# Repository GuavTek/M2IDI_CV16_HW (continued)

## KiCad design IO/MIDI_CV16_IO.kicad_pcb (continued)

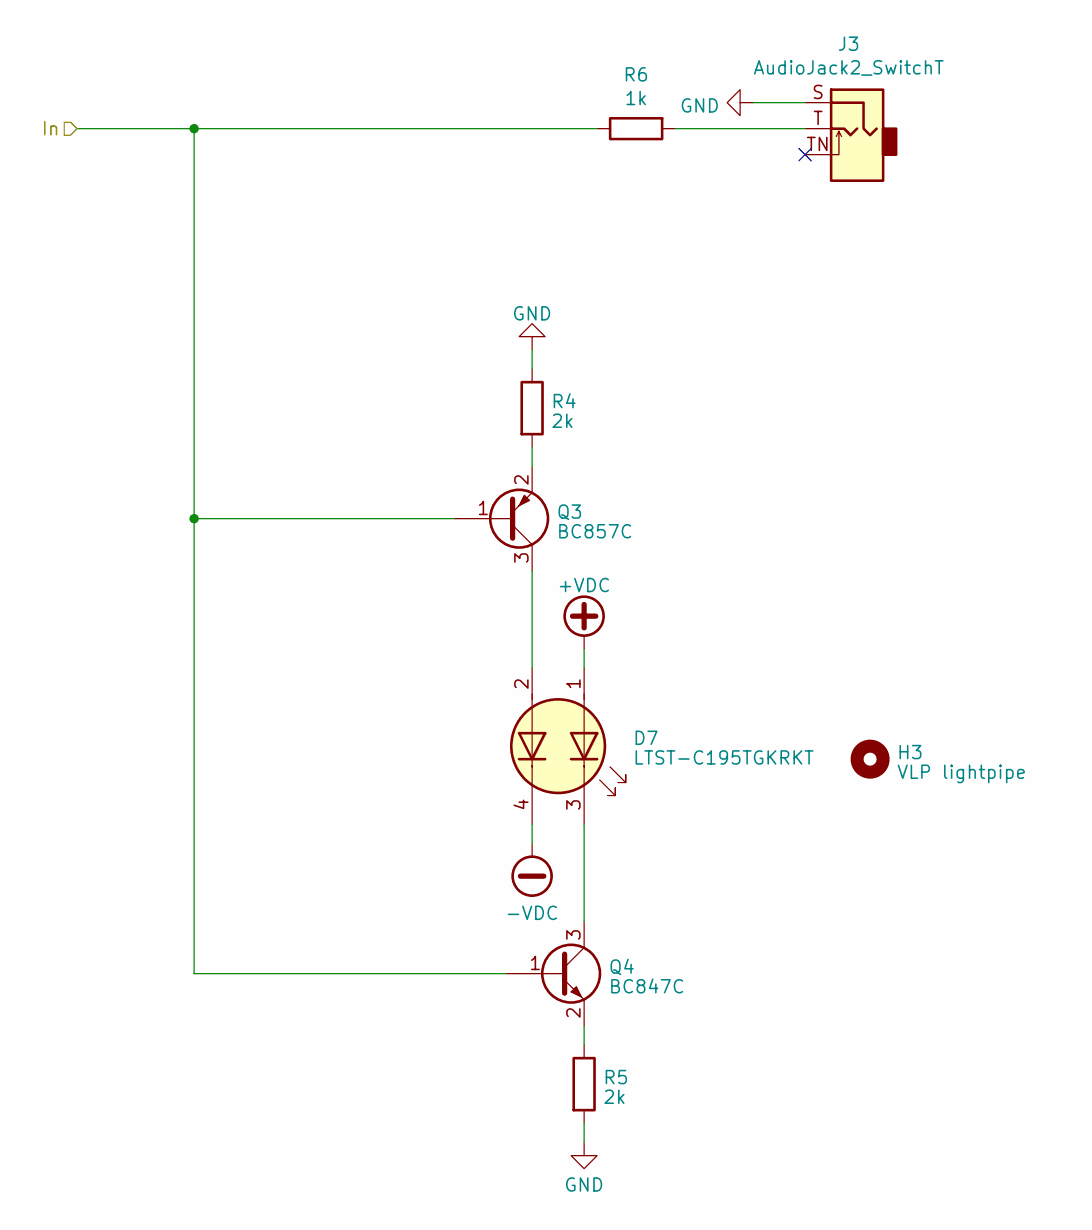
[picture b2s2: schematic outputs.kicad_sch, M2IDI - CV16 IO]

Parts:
D7: LTST-C195TGKRKT; LED_LiteOn_LTST-C195TGKRKT
H3: VLP lightpipe; VLP-LightPipes
J3: AudioJack2_SwitchT; PJ398SM
Q3: BC857C; SOT-23
Q4: BC847C; SOT-23
R4, R5: 2k; R_0603_1608Metric
R6: 1k; R_0603_1608Metric

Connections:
+VDC: D7.1 (A1); also elsewhere on the board
-VDC: D7.4 (K2); also elsewhere on the board
/Outputs1/In: Q3.1 (B), Q4.1 (B), R6.1; also elsewhere on the board
GND: J3.S, R4.1, R5.2; also elsewhere on the board
unnamed: D7.2 (A2), Q3.3 (C)
unnamed: D7.3 (K1), Q4.3 (C)
unnamed: J3.T, R6.2
unnamed: Q3.2 (E), R4.2
unnamed: Q4.2 (E), R5.1

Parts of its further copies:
D10, D13, D16, D19, D61, D64, D67, D70, D73, D76, D79, D82, D85, D88, D91: LTST-C195TGKRKT; LED_LiteOn_LTST-C195TGKRKT
H1, H2, H4, H5, H6, H7, H8, H9, H10, H11, H12, H13, H14, H15, H16: VLP lightpipe; VLP-LightPipes
J4, J5, J6, J7, J8, J9, J10, J12, J13, J14, J15, J16, J17, J18, J19: AudioJack2_SwitchT; PJ398SM
Q5, Q7, Q9, Q11, Q13, Q15, Q17, Q19, Q21, Q23, Q25, Q27, Q29, Q31, Q33: BC857C; SOT-23
Q6, Q8, Q10, Q12, Q14, Q16, Q18, Q20, Q22, Q24, Q26, Q28, Q30, Q32, Q34: BC847C; SOT-23
R7, R8, R10, R11, R13, R14, R16, R17, R19, R20, R22, R23, R25, R26, R28, R29, R31, R32, R34, R35, R37, R38, R40, R41, R43, R44, R46, R47, R49, R50: 2k; R_0603_1608Metric
R9, R12, R15, R18, R21, R24, R27, R30, R33, R36, R39, R42, R45, R48, R51: 1k; R_0603_1608Metric

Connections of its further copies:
+VDC: D10.1 (A1), D13.1 (A1), D16.1 (A1), D19.1 (A1), D61.1 (A1), D64.1 (A1), D67.1 (A1), D70.1 (A1), D73.1 (A1), D76.1 (A1), D79.1 (A1), D82.1 (A1), D85.1 (A1), D88.1 (A1), D91.1 (A1); also elsewhere on the board
-VDC: D10.4 (K2), D13.4 (K2), D16.4 (K2), D19.4 (K2), D61.4 (K2), D64.4 (K2), D67.4 (K2), D70.4 (K2), D73.4 (K2), D76.4 (K2), D79.4 (K2), D82.4 (K2), D85.4 (K2), D88.4 (K2), D91.4 (K2); also elsewhere on the board
/Outputs2/In: Q5.1 (B), Q6.1 (B), R9.1; also elsewhere on the board
/Outputs3/In: Q7.1 (B), Q8.1 (B), R12.1; also elsewhere on the board
/Outputs4/In: Q9.1 (B), Q10.1 (B), R15.1; also elsewhere on the board
/Outputs5/In: Q11.1 (B), Q12.1 (B), R18.1; also elsewhere on the board
/Outputs6/In: Q13.1 (B), Q14.1 (B), R21.1; also elsewhere on the board
/Outputs7/In: Q15.1 (B), Q16.1 (B), R24.1; also elsewhere on the board
/Outputs8/In: Q17.1 (B), Q18.1 (B), R27.1; also elsewhere on the board
/Outputs9/In: Q19.1 (B), Q20.1 (B), R30.1; also elsewhere on the board
/Outputs10/In: Q21.1 (B), Q22.1 (B), R33.1; also elsewhere on the board
/Outputs11/In: Q23.1 (B), Q24.1 (B), R36.1; also elsewhere on the board
/Outputs12/In: Q25.1 (B), Q26.1 (B), R39.1; also elsewhere on the board
/Outputs13/In: Q27.1 (B), Q28.1 (B), R42.1; also elsewhere on the board
/Outputs14/In: Q29.1 (B), Q30.1 (B), R45.1; also elsewhere on the board
/Outputs15/In: Q31.1 (B), Q32.1 (B), R48.1; also elsewhere on the board
/Outputs16/In: Q33.1 (B), Q34.1 (B), R51.1; also elsewhere on the board
GND: J4.S, J5.S, J6.S, J7.S, J8.S, J9.S, J10.S, J12.S, J13.S, J14.S, J15.S, J16.S, J17.S, J18.S, J19.S, R7.1, R8.2, R10.1, R11.2, R13.1, R14.2, R16.1, R17.2, R19.1, R20.2, R22.1, R23.2, R25.1, R26.2, R28.1, R29.2, R31.1, R32.2, R34.1, R35.2, R37.1, R38.2, R40.1, R41.2, R43.1, R44.2, R46.1, R47.2, R49.1, R50.2; also elsewhere on the board
unnamed: D10.2 (A2), Q5.3 (C)
unnamed: D10.3 (K1), Q6.3 (C)
unnamed: D13.2 (A2), Q7.3 (C)
unnamed: D13.3 (K1), Q8.3 (C)
unnamed: D16.2 (A2), Q9.3 (C)
unnamed: D16.3 (K1), Q10.3 (C)
unnamed: D19.2 (A2), Q11.3 (C)
unnamed: D19.3 (K1), Q12.3 (C)
unnamed: D61.2 (A2), Q13.3 (C)
unnamed: D61.3 (K1), Q14.3 (C)
unnamed: D64.2 (A2), Q15.3 (C)
unnamed: D64.3 (K1), Q16.3 (C)
unnamed: D67.2 (A2), Q17.3 (C)
unnamed: D67.3 (K1), Q18.3 (C)
unnamed: D70.2 (A2), Q19.3 (C)
unnamed: D70.3 (K1), Q20.3 (C)
unnamed: D73.2 (A2), Q21.3 (C)
unnamed: D73.3 (K1), Q22.3 (C)
unnamed: D76.2 (A2), Q23.3 (C)
unnamed: D76.3 (K1), Q24.3 (C)
unnamed: D79.2 (A2), Q25.3 (C)
unnamed: D79.3 (K1), Q26.3 (C)
unnamed: D82.2 (A2), Q27.3 (C)
unnamed: D82.3 (K1), Q28.3 (C)
unnamed: D85.2 (A2), Q29.3 (C)
unnamed: D85.3 (K1), Q30.3 (C)
unnamed: D88.2 (A2), Q31.3 (C)
unnamed: D88.3 (K1), Q32.3 (C)
unnamed: D91.2 (A2), Q33.3 (C)
unnamed: D91.3 (K1), Q34.3 (C)
unnamed: J4.T, R9.2
unnamed: J5.T, R12.2
unnamed: J6.T, R15.2
unnamed: J7.T, R18.2
unnamed: J8.T, R21.2
unnamed: J9.T, R24.2
unnamed: J10.T, R27.2
unnamed: J12.T, R30.2
unnamed: J13.T, R33.2
unnamed: J14.T, R36.2
unnamed: J15.T, R39.2
unnamed: J16.T, R42.2
unnamed: J17.T, R45.2
unnamed: J18.T, R48.2
unnamed: J19.T, R51.2
unnamed: Q5.2 (E), R7.2
unnamed: Q6.2 (E), R8.1
unnamed: Q7.2 (E), R10.2
unnamed: Q8.2 (E), R11.1
unnamed: Q9.2 (E), R13.2
unnamed: Q10.2 (E), R14.1
unnamed: Q11.2 (E), R16.2
unnamed: Q12.2 (E), R17.1
unnamed: Q13.2 (E), R19.2
unnamed: Q14.2 (E), R20.1
unnamed: Q15.2 (E), R22.2
unnamed: Q16.2 (E), R23.1
unnamed: Q17.2 (E), R25.2
unnamed: Q18.2 (E), R26.1
unnamed: Q19.2 (E), R28.2
unnamed: Q20.2 (E), R29.1
unnamed: Q21.2 (E), R31.2
unnamed: Q22.2 (E), R32.1
unnamed: Q23.2 (E), R34.2
unnamed: Q24.2 (E), R35.1
unnamed: Q25.2 (E), R37.2
unnamed: Q26.2 (E), R38.1
unnamed: Q27.2 (E), R40.2
unnamed: Q28.2 (E), R41.1
unnamed: Q29.2 (E), R43.2
unnamed: Q30.2 (E), R44.1
unnamed: Q31.2 (E), R46.2
unnamed: Q32.2 (E), R47.1
unnamed: Q33.2 (E), R49.2
unnamed: Q34.2 (E), R50.1

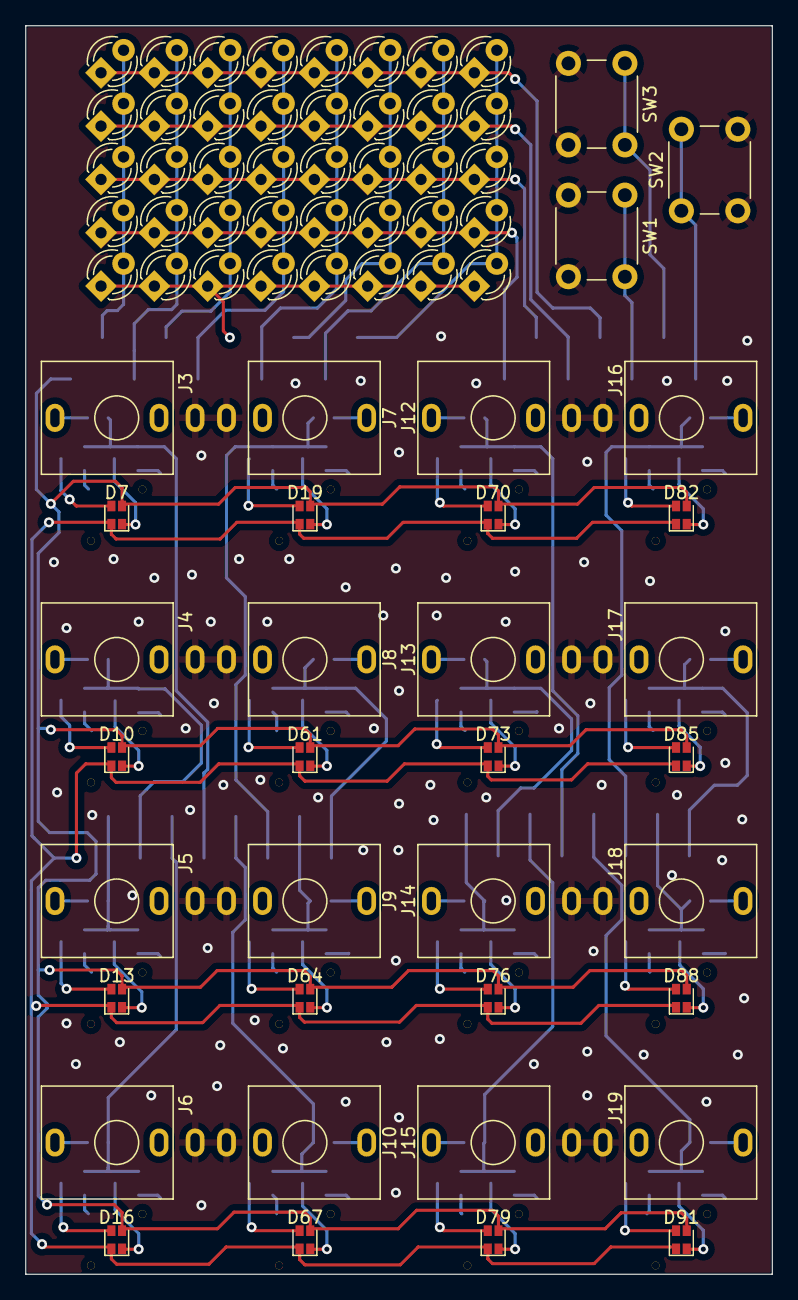
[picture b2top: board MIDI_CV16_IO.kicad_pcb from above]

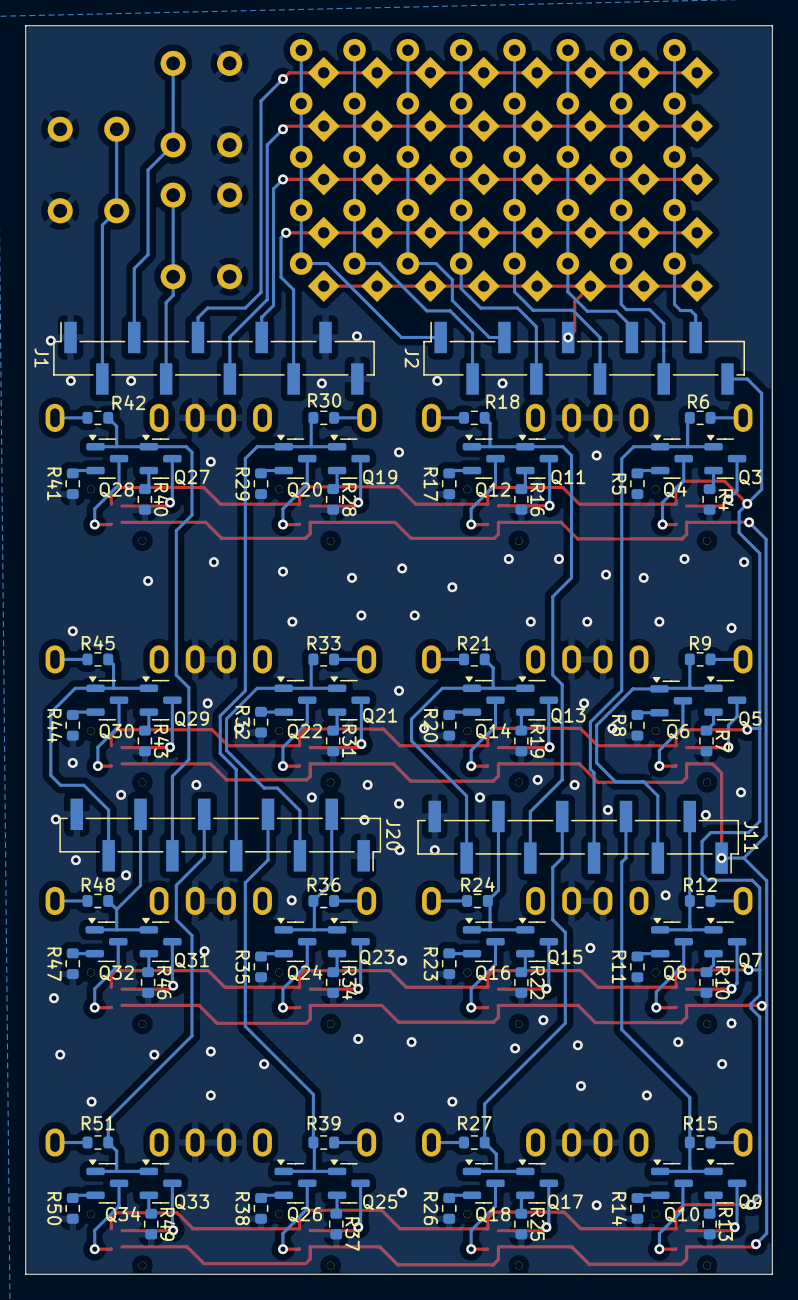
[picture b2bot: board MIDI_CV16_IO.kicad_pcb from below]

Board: 2 copper layers, 59.5 x 99.5 mm, 175 parts (84 on the bottom side), 115 nets.

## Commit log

2022-02-17 Add files
2022-02-17 Update termination circuit
2022-02-17 Backlink to CADLAB.io has been added.
2022-02-18 Add custom symbols and footprints
2022-02-18 Fix DRC errors
2023-04-08 Update front panel
2023-04-19 Update to KiCAD 7
2023-05-07 Fix DRC
2023-05-07 Fix front panel DRC
2023-05-07 Fix more DRC
2023-05-07 Maybe actually fix drc
2023-05-07 Fix net-tie attributes
2023-05-10 Minor fixes
2023-05-11 Shrink crystal fp and add silkscreen text
2023-05-11 Consolidate resistor values
2023-05-14 Improve USB impedance and power headroom
2023-07-09 Change CAN tranceiver to MCP2562
2023-07-09 Fix 2x8 header footprint
2023-07-09 Fix crystal footprint
2023-07-09 Fix DRC warnings
2023-07-09 Fix more drc warnings........
2023-09-01 Finalize module
2024-03-30 Add message about peak-detectors on IO leds
2024-03-30 Remove IO peak-detectors
2024-03-31 Switch from CC LICENSE to CERN open hardware license
2024-06-11 Specify dielectric type of SnH caps
2024-06-12 Change SPI bus for EEPROM
2024-06-12 Increase SnH capacitance
2024-06-16 Layout v3.1
2024-06-16 Add drc filter to kibot
2024-06-16 Add error number in kibot filter
2024-06-16 Update to kicad 8
